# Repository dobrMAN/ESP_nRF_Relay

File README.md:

# ESP_nRF_Relay

Реле для управления освещением на базе ESP8266 и nRF24L01+

Релейная часть программно аппартного комплекса для управления освещением или другими нагрузками.

Реле реализовано на базе симистора BTA16-600 и управляется WiFi модулем ESP8266 (ESP-03) и подключенным к нему радио модулем nRF24L01+ mini.

**Программная часть:**

Будет дорабатываться в плане настройки готового модуля.

На данный момент программная часть вполне работоспособна и тестируется на макетной плате.

**Аппаратная часть:**

Плата и схема в разработке. Плата не готова к производству, это лишь наброски, который требуется доработать и перепроверить.

**Ссылки на компоненты:**

+ BTA16-600 - http://www.ebay.com/sch/i.html?_from=R40&_trksid=p2050601.m570.l1313.TR0.TRC0.H0.TRS0&_nkw=bta16-600b&_sacat=0

+ MOC3061 - http://www.ebay.com/sch/i.html?_from=R40&_trksid=p2050601.m570.l1313.TR11.TRC1.A0.H0.Xmoc3061.TRS0&_nkw=moc3061&_sacat=0

+ ESP-03 - http://www.ebay.com/sch/i.html?_odkw=moc3061&_osacat=0&_from=R40&_trksid=p2045573.m570.l1313.TR12.TRC2.A0.H0.XESP-03.TRS0&_nkw=ESP-03&_sacat=0

+ nRF24 - http://www.ebay.com/sch/i.html?_odkw=ESP-03&_osacat=0&_from=R40&_trksid=p2045573.m570.l1313.TR1.TRC0.A0.H0.XnRF24l01+smd.TRS0&_nkw=nRF24l01+smd&_sacat=0

+ AC/DC - http://www.ebay.com/sch/i.html?_odkw=nRF24l01+smd&_osacat=0&_from=R40&_trksid=p2045573.m570.l1313.TR8.TRC2.A0.H0.XAC%2FDC+5v.TRS0&_nkw=AC%2FDC+5v&_sacat=0

+ И разная мелочевка.

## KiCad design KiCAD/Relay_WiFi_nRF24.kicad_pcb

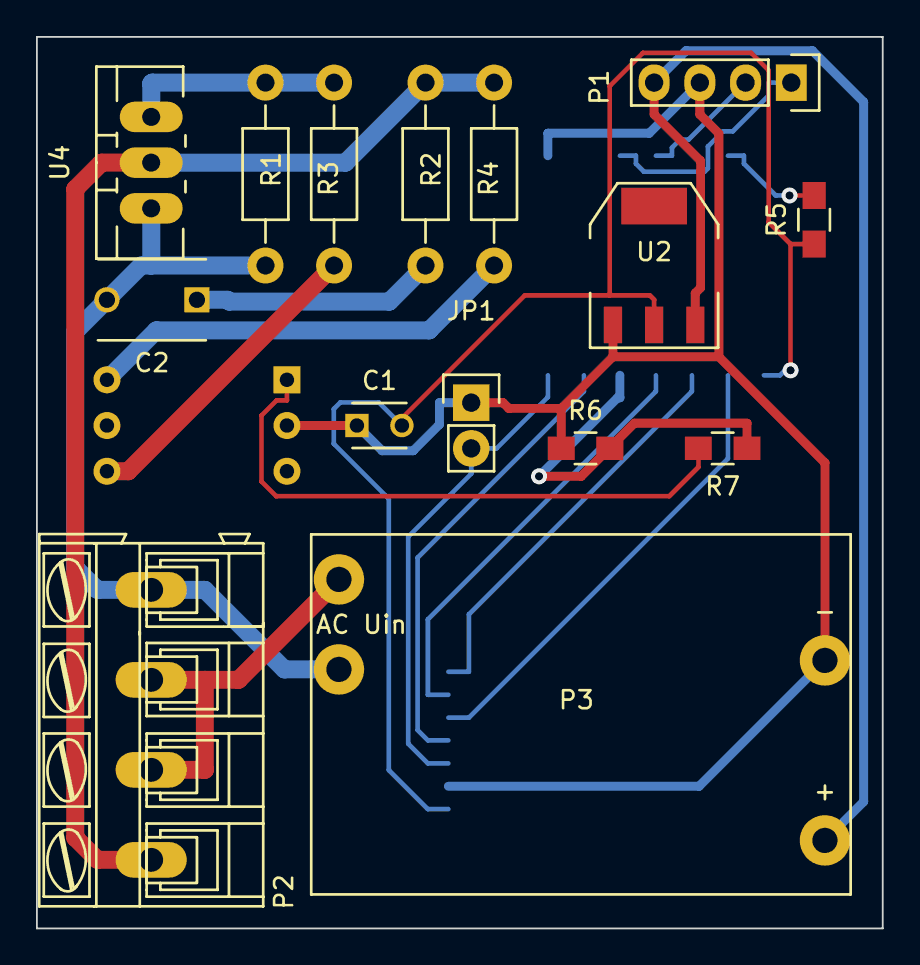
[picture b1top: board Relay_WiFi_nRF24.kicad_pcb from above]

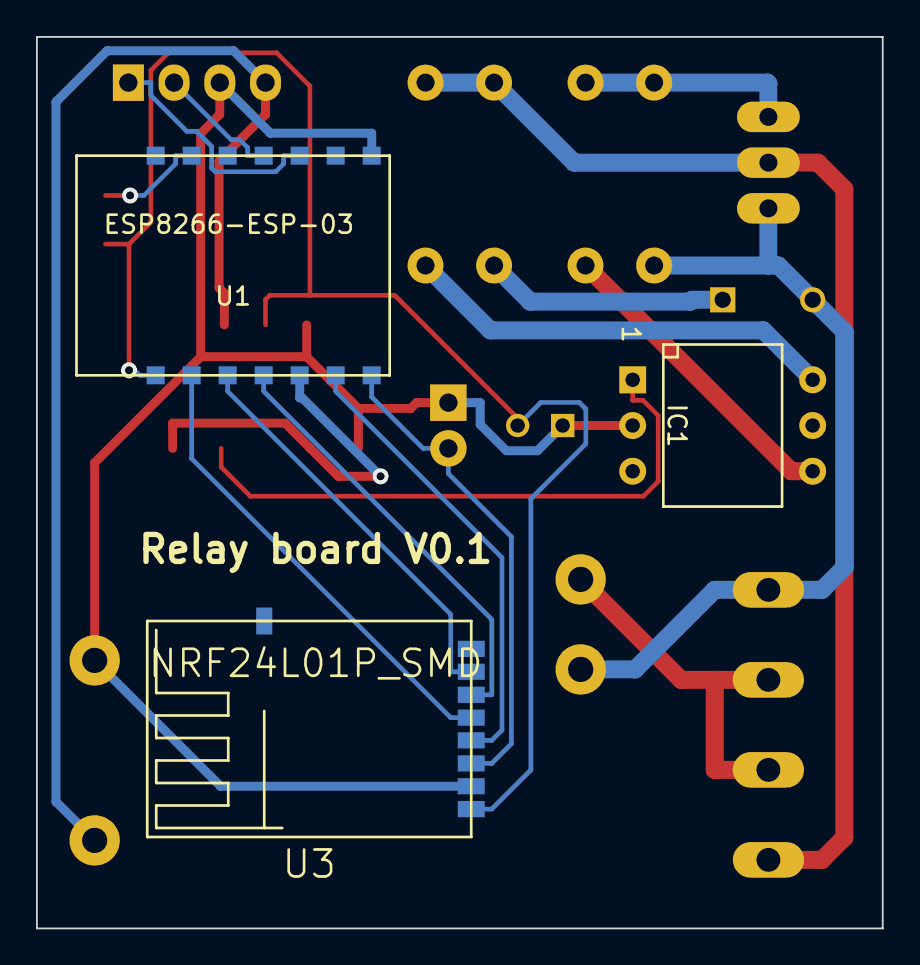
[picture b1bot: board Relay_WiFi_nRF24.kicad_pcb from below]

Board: 2 copper layers, 47.0 x 49.5 mm, 18 parts (3 on the bottom side), 20 nets.

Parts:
C1: 0.01; C_Disc_D3_P2.5
C2: 10n; C_Disc_D6_P5
IC1: MOC3061M; Optocoupler_6pin_wide_Stile-II
JP1: JUMPER; Pin_Header_Straight_1x02
P1: CONN_4; Pin_Header_Straight_1x04
P2: CONN_4; AK300-4
P3: CONN_01X04; ACDC-FromEbay-5V-700A
R1: 10k; Resistor_Horizontal_RM10mm
R2, R3: 360; Resistor_Horizontal_RM10mm
R4: 39; Resistor_Horizontal_RM10mm
R5, R6: 10k; R_0805_HandSoldering
R7: 220; R_0805_HandSoldering
U1: ESP8266-ESP-03
U2: NCP1117ST33T3G; SOT-223
U3: NRF24L01P_SMD
U4: BTA16; TO-220_Neutral123_Vertical_LargePads

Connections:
GND: C1.1, IC1.2, JP1.1, P1.3, P3.4, R6.1, U1.1, U2.1, U3.2
unnamed: C1.2, R5.1, U1.8, U2.2, U3.1
unnamed: C2.1, R4.2
unnamed: C2.2, P2.4, P3.2, R3.2, U4.1
unnamed: IC1.1, R7.2
unnamed: IC1.4, R1.1
unnamed: IC1.6, R2.1
unnamed: JP1.2, U1.14, U3.3
unnamed: P1.1, U1.3
unnamed: P1.2, U1.4
unnamed: P2.1, R2.2, R4.1, U4.2
unnamed: P2.2, P2.3, P3.1
unnamed: R1.2, R3.1, U4.3
unnamed: R5.2, U1.6
unnamed: R6.2, R7.1, U1.12
unnamed: U1.9, U3.5
unnamed: U1.10, U3.7
unnamed: U1.11, U3.6
unnamed: U1.13, U3.4
VCC: P1.4, P3.3, U2.3

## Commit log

2015-10-23 :tada: Added .gitattributes & .gitignore files
2015-10-23 Initial release
2015-10-24 Мелкие изменения
2015-10-24 Add Gitter badge
2015-10-25 Изменение прототипа платы
    Развернул радиомодули, переложил дорожки, увеличил ширину дорожек
    силовой части
2015-10-25 Update last commit
2015-10-25 Замена посадочного места блока питания 5V
    Изменил посадочное место блока питания под размеры китайского БП с
    Ebay.com AC/DC-5V-700A
2015-10-25 Файлы для производства
2015-10-25 Fix изменен путь до библиотект проэкта
2015-10-26 Правка схемы
    Добавлены недостающие подтягивающие резисторы.
    Исправлена библиотека посадочного места коннектора для подключения сети
    и нагрузки.
    Исправлена толщина дорожек.
    Уменьшен размер платы.
2015-10-26 Изменения в схеме
    Добавлен токоограничивающий резистр.
    Мелкие правки печатной платы.
2015-10-28 [Схема] Надпись на печатной плате
    Просто добавил надпись
2015-11-13 Дополнил описание
2017-04-15 Test
